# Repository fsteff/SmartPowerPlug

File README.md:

# SmartPowerPlug
A Raspberry PI based power plug that measures the energy.
It is able to turn on/off the power if necessary, based on a shell script to be highly customizeable.

The webinterface displays the measured values on an interactive graph (using Rickshaw).

------------------------------------------------------------------------
SOFTWARE:
------------------------------------------------------------------------
Needed programs:
 - Apache 2 (or a similar webserver)
 - php5 and php-cli
 - php5-sqlite
 - SQLite3

PHP Dependencies:
 - PhpSerial
 - System_Daemon
 
JS Dependencies:
 - Rickshaw
 - D3
 - JQuery
 - JQuery UI
 - Menumaker

All the dependencies are included in the source.

------------------------------------------------------------------------
HARDWARE:
------------------------------------------------------------------------
The energy measurement is based on the MCP39F501, which communciates over RS485.

------------------------------------------------------------------------
Known issues:
------------------------------------------------------------------------
- After a reboot the serial (uart) has to be opened by an other program - if this is not the case, the raspberry answers with some rubbish sequences...
- The calibration of the MCP39F501 is invalid - maybe there is a problem with the print.

You can download a preinstalled raspbian image here:
https://mega.co.nz/#F!rpBVlAKI!rYRUqPWmyS1goKNWMSgLuQ

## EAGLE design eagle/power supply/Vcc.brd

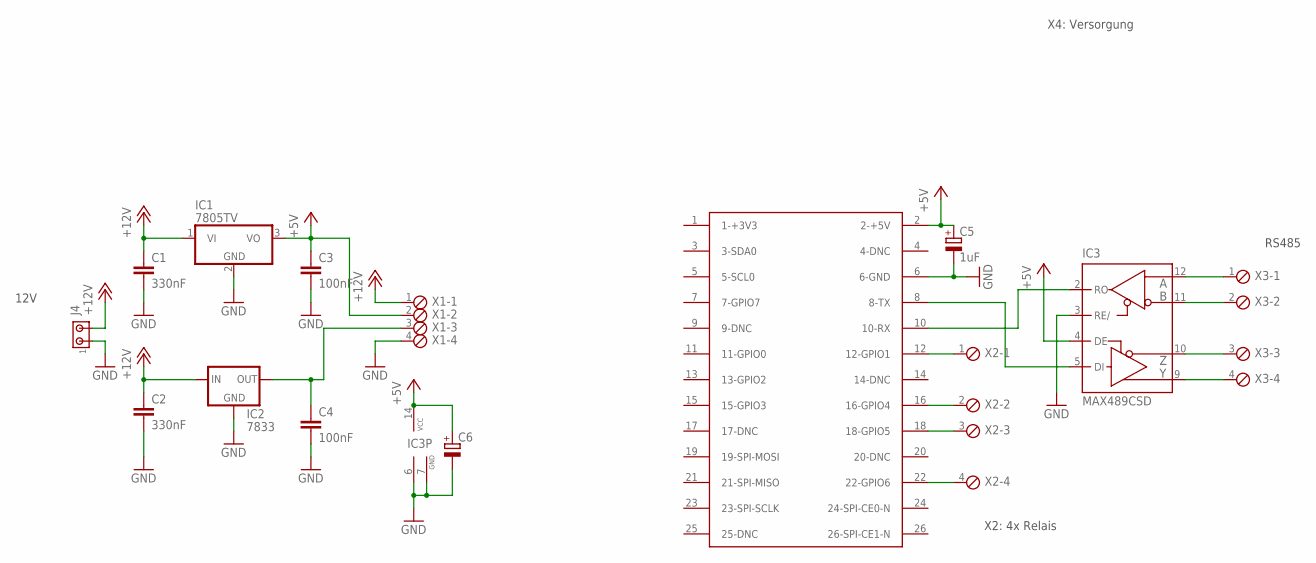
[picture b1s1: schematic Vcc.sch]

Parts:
C1, C2: 330nF; C050-035X075
C3, C4: 100nF; C050-035X075
C5: 1uF; E2,5-7
C6: CPOL-EUE2.5-7; E2,5-7
IC1: 7805TV; TO220V
IC2: 7833; 78XXS
IC3: MAX489CSD; SO14
J4: MTA02-100; 10X02MTA
U$1: RASPBERRY-PI
X1, X2, X3: MPT4; 4POL254

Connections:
+5V: C3.1, C5.+, C6.+, IC1.3 (VO), IC3.4 (DE), IC3.14 (VCC), U$1.2 (2-+5V), X1.2
+12V: C1.1, C2.1, IC1.1 (VI), IC2.IN, J4.2, X1.1
GND: C1.2, C2.2, C3.2, C4.2, C5.-, C6.-, IC1.2 (GND), IC2.GND, IC3.3 (RE/), IC3.6 (GND), IC3.7 (GND), J4.1, U$1.6 (6-GND), X1.4
unnamed: U$1.18 (18-GPIO5), X2.3
unnamed: U$1.22 (22-GPIO6), X2.4
unnamed: IC3.11 (B), X3.2
unnamed: IC3.2 (RO), U$1.10 (10-RX)
unnamed: IC3.5 (DI), U$1.8 (8-TX)
unnamed: IC3.9 (Y), X3.4
unnamed: IC3.10 (Z), X3.3
unnamed: IC3.12 (A), X3.1
unnamed: U$1.16 (16-GPIO4), X2.2
unnamed: C4.1, IC2.OUT, X1.3
unnamed: U$1.12 (12-GPIO1), X2.1

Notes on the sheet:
12V
X2: 4x Relais
X4: Versorgung
RS485

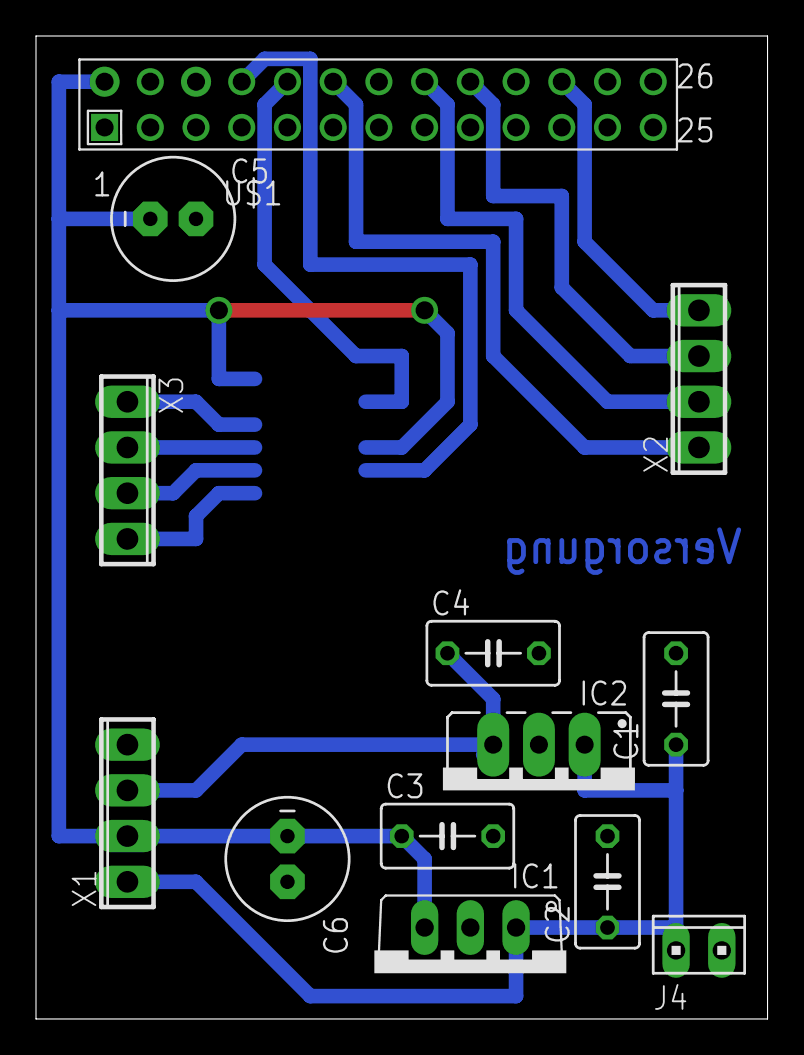
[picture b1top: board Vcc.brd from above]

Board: 2 copper layers, 40.6 x 54.6 mm, 14 parts (1 on the bottom side), 14 nets.

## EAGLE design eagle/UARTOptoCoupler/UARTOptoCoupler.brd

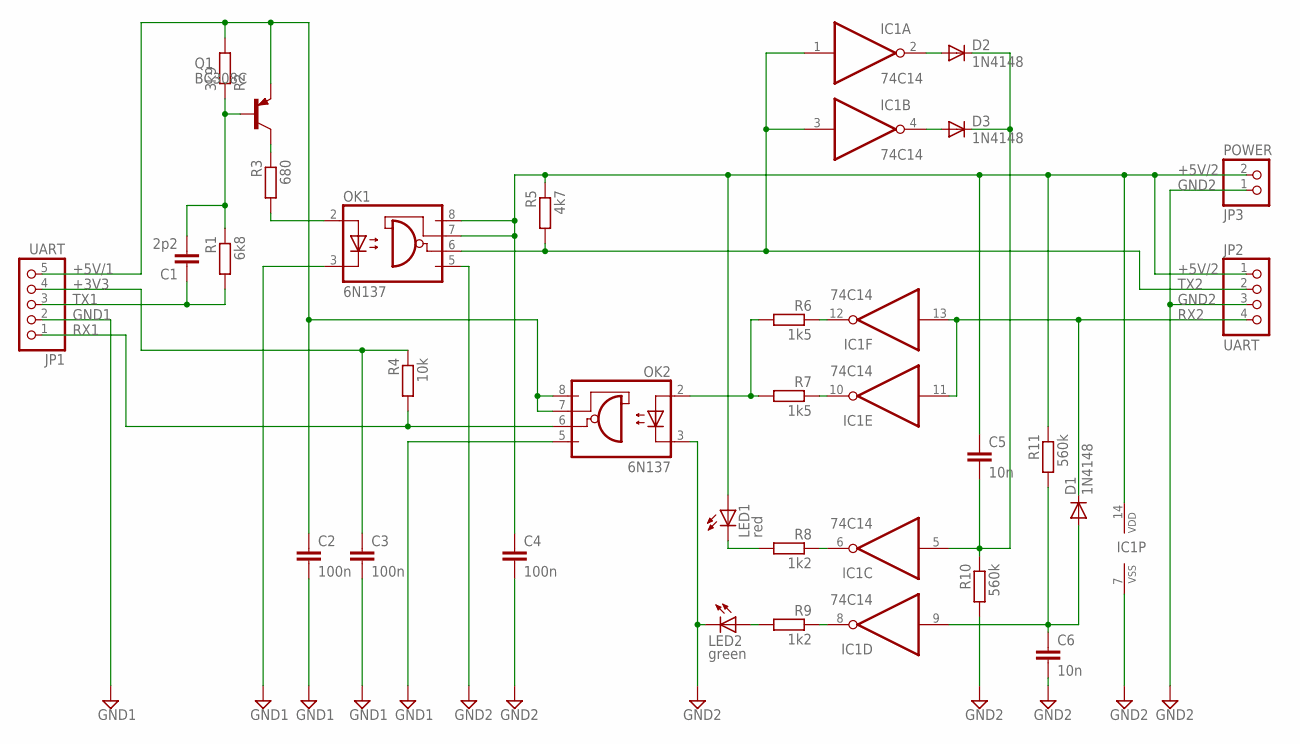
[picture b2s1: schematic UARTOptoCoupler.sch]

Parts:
C1: 2p2; C025-024X044
C2, C3, C4: 100n; C050-025X075
C5, C6: 10n; C050-025X075
D1, D2, D3: 1N4148; DO35-10
IC1: 74C14; DIL14
JP1: UART; 1X05
JP2: UART; 1X04/90
JP3: POWER; 1X02
LED1: red; LED3MM
LED2: green; LED3MM
OK1, OK2: 6N137; DIL08
Q1: BC308C; TO92
R1: 6k8; 0207/10
R2: 3k9; 0207/10
R3: 680; 0207/10
R4: 10k; 0207/10
R5: 4k7; 0207/10
R6, R7: 1k5; 0207/10
R8, R9: 1k2; 0207/10
R10, R11: 560k; 0207/10

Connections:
+3V3: C3.1, JP1.4, R4.1
+5V/1: C2.1, JP1.5, OK2.7 (VE), OK2.8 (VCC), Q1.1 (E), R2.2
+5V/2: C4.1, C5.1, IC1.14 (VDD), JP2.1, JP3.2, LED1.A, OK1.7 (VE), OK1.8 (VCC), R5.1, R11.1
GND1: C2.2, C3.2, JP1.2, OK1.3 (C), OK2.5 (GND)
GND2: C4.2, C6.2, IC1.7 (VSS), JP2.3, JP3.1, LED2.K (C), OK1.5 (GND), OK2.3 (C), R10.2
N1: C1.2, Q1.2 (B), R1.1, R2.1
unnamed: OK1.2 (A), R3.2
unnamed: LED1.K (C), R8.2
unnamed: Q1.3 (C), R3.1
unnamed: OK2.2 (A), R6.2, R7.2
unnamed: C5.2, D2.C, D3.C, IC1.5 (I), R10.1
unnamed: IC1.12 (O), R6.1
unnamed: IC1.10 (O), R7.1
unnamed: C6.1, D1.A, IC1.9 (I), R11.2
unnamed: IC1.6 (O), R8.1
unnamed: IC1.8 (O), R9.1
unnamed: D3.A, IC1.4 (O)
unnamed: LED2.A, R9.2
unnamed: D2.A, IC1.2 (O)
RX1: JP1.1, OK2.6 (VO), R4.2
RX2: D1.C, IC1.11 (I), IC1.13 (I), JP2.4
TX1: C1.1, JP1.3, R1.2
TX2: IC1.1 (I), IC1.3 (I), JP2.2, OK1.6 (VO), R5.2

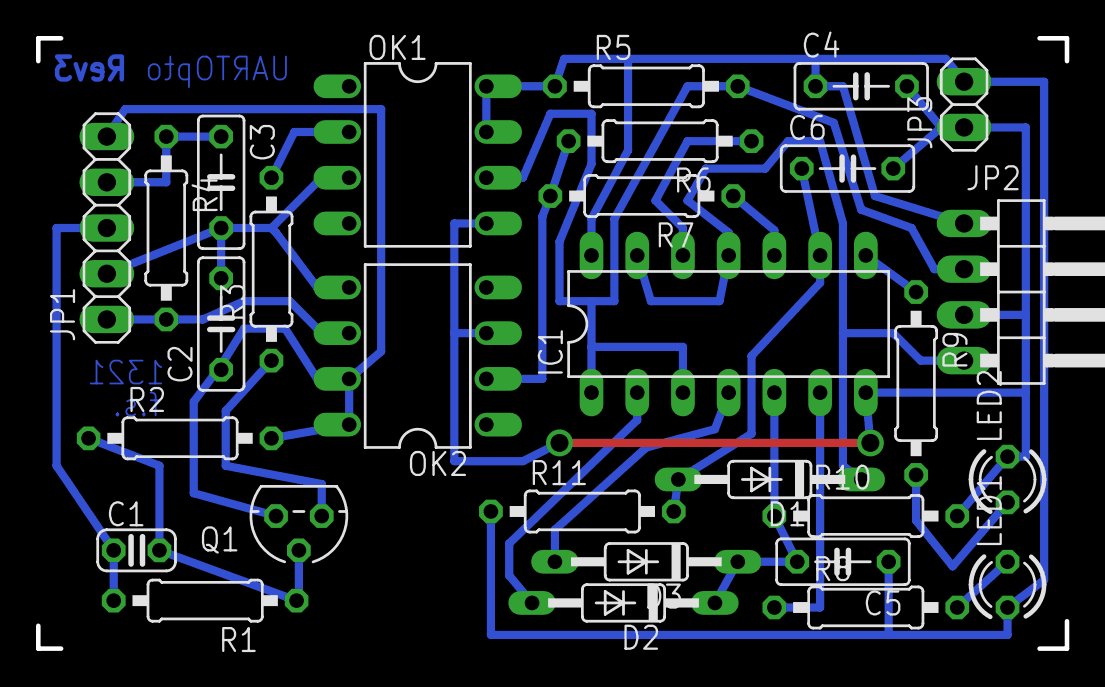
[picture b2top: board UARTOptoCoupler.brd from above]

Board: 2 copper layers, 57.1 x 33.9 mm, 29 parts (0 on the bottom side), 23 nets.

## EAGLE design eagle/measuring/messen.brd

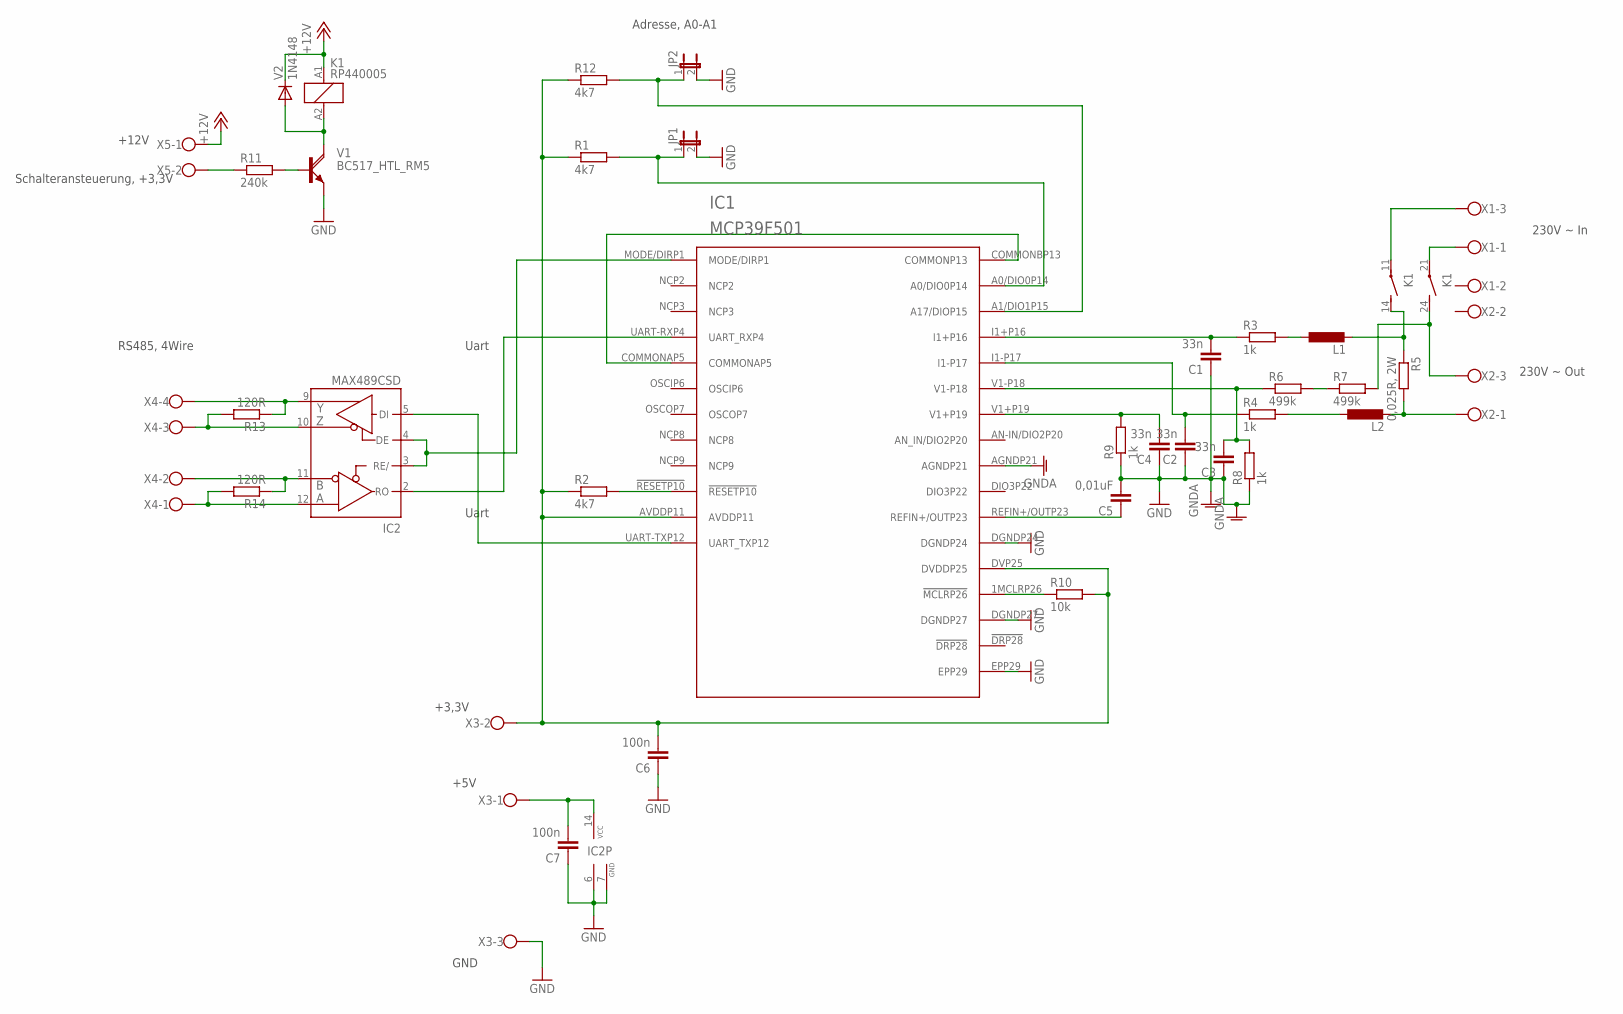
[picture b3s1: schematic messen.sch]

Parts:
C1, C2, C3, C4: 33n; C0805K
C5: 0,01uF; C0805K
C6, C7: 100n; C0805K
IC1: MCP39F501
IC2: MAX489CSD; SO14
JP1, JP2: JP1E; JP1
K1: RP440005; RP440
L1, L2: L-EUL3230M; L3230M
R1, R12: 4k7; R0805
R2: 4k7; 0411/15
R3, R4, R8, R9: 1k; R0805
R5: 0,025R, 2W; R2512
R6, R7: 499k; 0411/15
R10: 10k; 0204/7
R11: 240k; 0411/15
R13, R14: 120R; R0805
V1: BC517_HTL_RM5; TO92_RM5
V2: 1N4148; DO35-7
X1, X2: W237-103_R
X3: W237-103_L
X4: W237-04P_L; W237-4P_L
X5: W237-102_L

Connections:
+12V: K1.A1 (1), V2.C, X5.1
GND: C1.1, C2.1, C3.1, C4.1, C5.2, C6.1, C7.1, IC1.AGNDP21, IC1.DGNDP24, IC1.DGNDP27, IC1.EPP29, IC2.6 (GND), IC2.7 (GND), JP1.2, JP2.2, R8.1, R9.1, V1.1 (E), X3.3
unnamed: R11.1, X5.2
unnamed: IC1.UART-RXP4 (UART_RXP4), IC2.2 (RO)
unnamed: IC1.MODE/DIRP1, IC2.3 (RE/), IC2.4 (DE)
unnamed: IC1.!RESETP10, R2.2
unnamed: C1.2, IC1.I1+P16, R3.1
unnamed: C2.2, IC1.I1-P17, R4.1
unnamed: C4.2, IC1.V1+P19, R9.2
unnamed: K1.A2 (2), V1.3 (C), V2.A
unnamed: L1.1, R3.2
unnamed: L2.1, R4.2
unnamed: L2.2, R5.2, X2.1
unnamed: K1.11, X1.3
unnamed: C5.1, IC1.REFIN+/OUTP23
unnamed: C3.2, IC1.V1-P18, R6.1, R8.2
unnamed: C6.2, IC1.AVDDP11, IC1.DVP25 (DVDDP25), R1.1, R2.1, R10.2, R12.1, X3.2
unnamed: IC1.1MCLRP26 (!MCLRP26), R10.1
unnamed: R11.2, V1.2 (B)
unnamed: R6.2, R7.1
unnamed: K1.14 (S), L1.2, R5.1
unnamed: K1.24 (S), R7.2, X2.3
unnamed: K1.21, X1.1
unnamed: IC1.UART-TXP12 (UART_TXP12), IC2.5 (DI)
unnamed: C7.2, IC2.14 (VCC), X3.1
unnamed: IC1.COMMONAP5, IC1.COMMONBP13 (COMMONP13)
unnamed: IC2.10 (Z), R13.2, X4.3
unnamed: IC2.9 (Y), R13.1, X4.4
unnamed: IC1.A0/DIO0P14, JP1.1, R1.2
unnamed: IC1.A1/DIO1P15 (A17/DIOP15), JP2.1, R12.2
unnamed: IC2.11 (B), R14.1, X4.2
unnamed: IC2.12 (A), R14.2, X4.1

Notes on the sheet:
230V ~ Out
230V ~ In
Adresse, A0-A1
+3,3V
GND
Uart
+5V
RS485, 4Wire
Schalteransteuerung, +3,3V
+12V

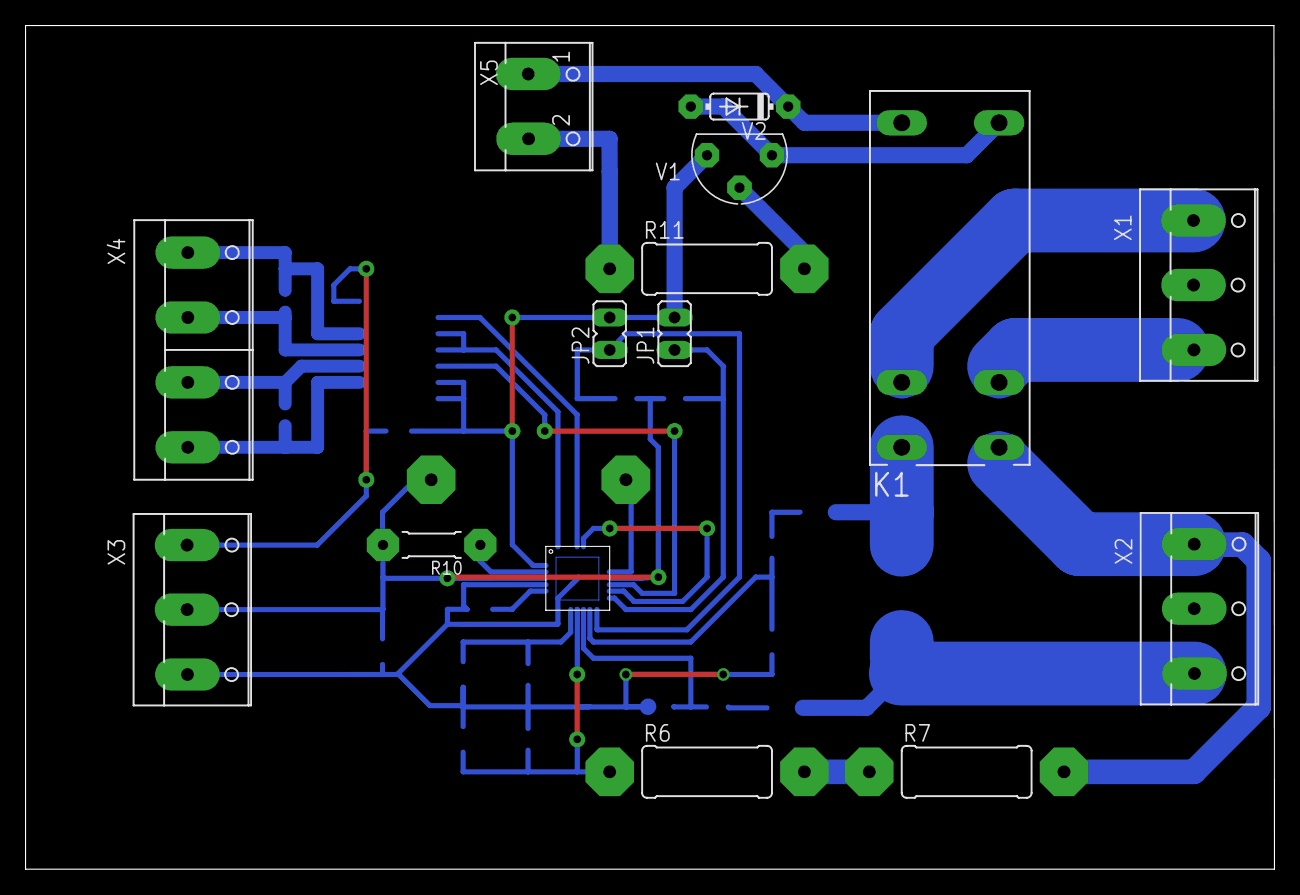
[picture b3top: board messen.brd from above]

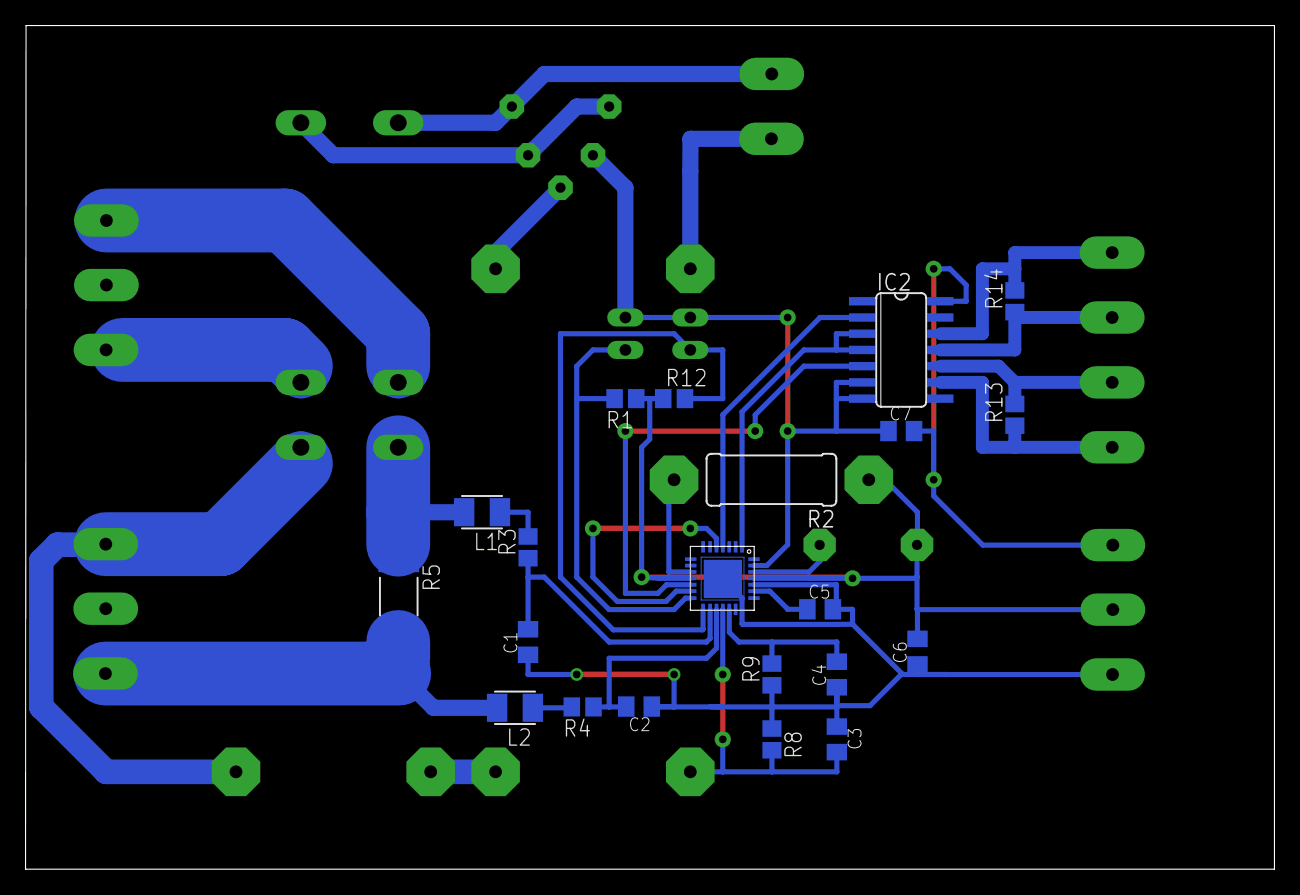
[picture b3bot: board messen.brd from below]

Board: 2 copper layers, 97.8 x 66.0 mm, 35 parts (21 on the bottom side), 32 nets.

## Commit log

2015-05-12 upload
    inital upload
2015-05-12 additions
    added (german) documentation
    added eagle circuit files
2015-05-12 remove
    remove useless thumbs.db
